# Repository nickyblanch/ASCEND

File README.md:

# ASCEND
All firmware &amp; mechanical design, and documentation for the UArizona SEDS ASCEND! team.

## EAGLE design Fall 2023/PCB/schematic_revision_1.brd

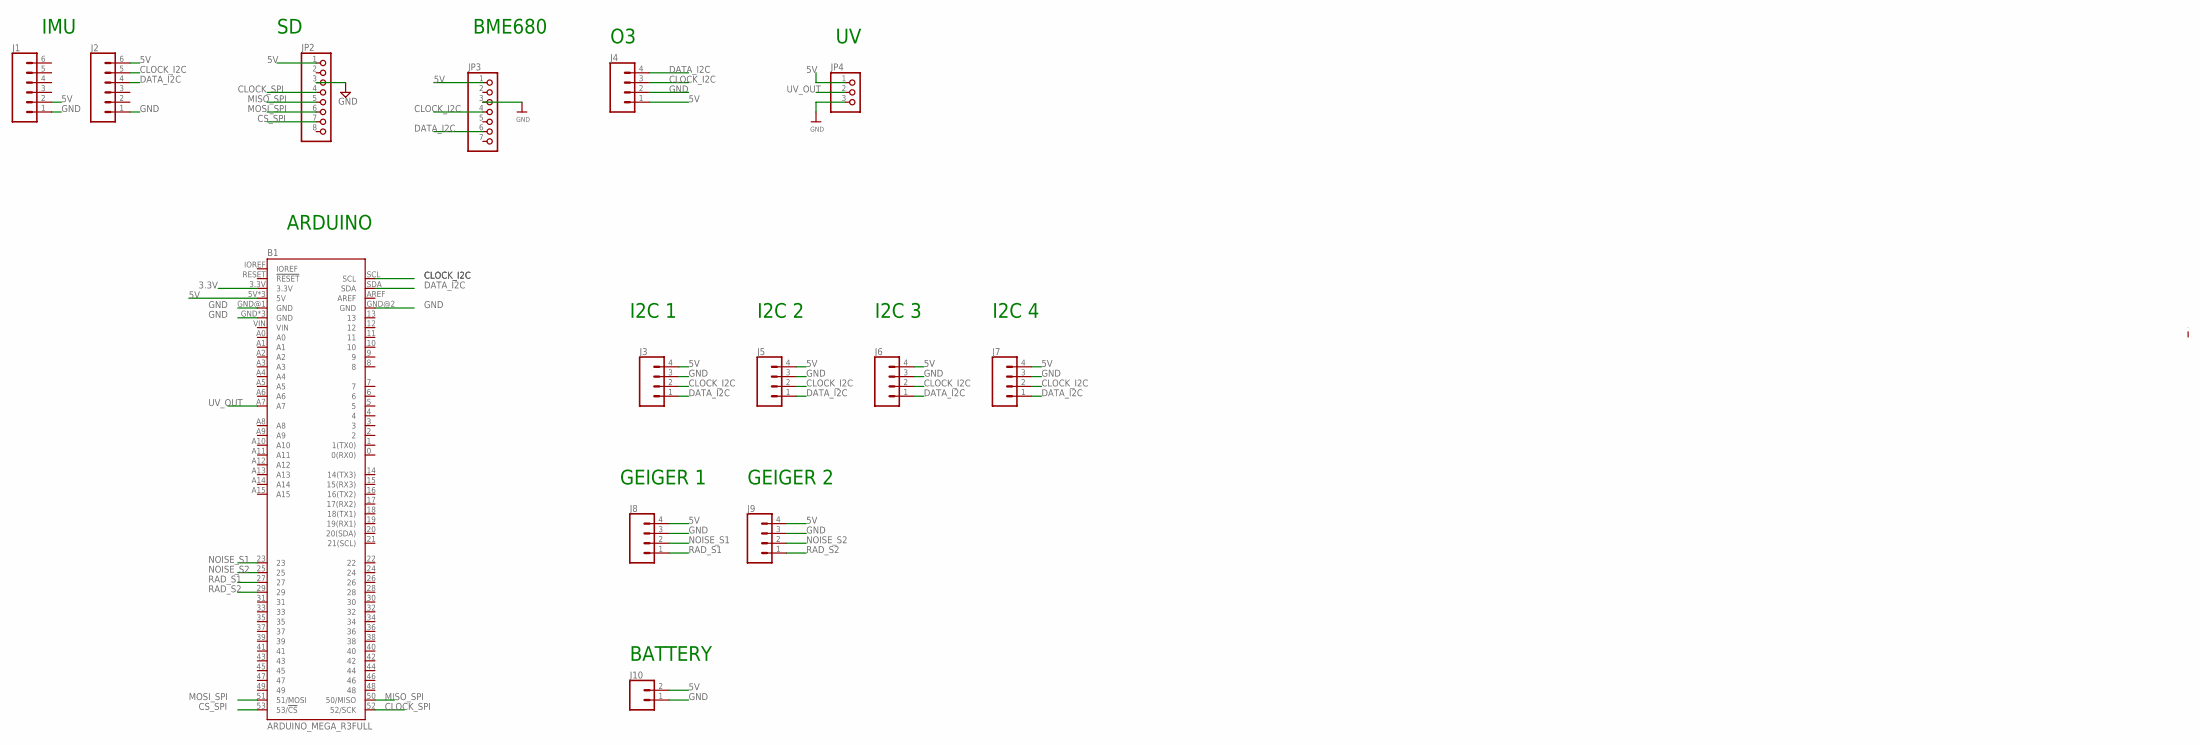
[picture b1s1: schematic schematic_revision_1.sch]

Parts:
B1: ARDUINO_MEGA_R3FULL; ARDUINO_MEGA_NO_SILK
J1, J2: CONN_06NO_SILK_NO_POP; 1X06_NO_SILK
J3, J5, J6, J7, J8, J9: CONN_04PTH; 1X04
J4: CONN_04LOCK; 1X04_LOCK
J10: CONN_02; 1X02
JP2: PINHD-1X8BIG; 1X08-BIG
JP3: HEADER-1X770MIL; 1X07_ROUND_70
JP4: PINHD-1X3CB; 1X03-CLEANBIG

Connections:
3.3V: B1.3.3V
5V: B1.5V, B1.5V@1 (5V), B1.5V@2 (5V), J1.2, J2.6, J3.4, J4.1, J5.4, J6.4, J7.4, J8.4, J9.4, J10.2, JP2.1, JP3.1, JP4.1
CLOCK_I2C: B1.SCL, J2.5, J3.2, J4.3, J5.2, J6.2, J7.2, JP3.4
CLOCK_SPI: B1.52 (52/SCK), JP2.4
CS_SPI: B1.53 (53/!CS), JP2.7
DATA_I2C: B1.SDA, J2.4, J3.1, J4.4, J5.1, J6.1, J7.1, JP3.6
GND: B1.GND, B1.GND@1 (GND), B1.GND@2 (GND), B1.GND@3 (GND), B1.GND@4 (GND), J1.1, J2.1, J3.3, J4.2, J5.3, J6.3, J7.3, J8.3, J9.3, J10.1, JP2.3, JP3.3, JP4.3
MISO_SPI: B1.50 (50/MISO), JP2.5
MOSI_SPI: B1.51 (51/MOSI), JP2.6
NOISE_S1: B1.23, J8.2
NOISE_S2: B1.25, J9.2
RAD_S1: B1.27, J8.1
RAD_S2: B1.29, J9.1
UV_OUT: B1.A7, JP4.2

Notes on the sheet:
IMU
ARDUINO
BME680
I2C 1
I2C 2
I2C 3
I2C 4
GEIGER 1
GEIGER 2
BATTERY

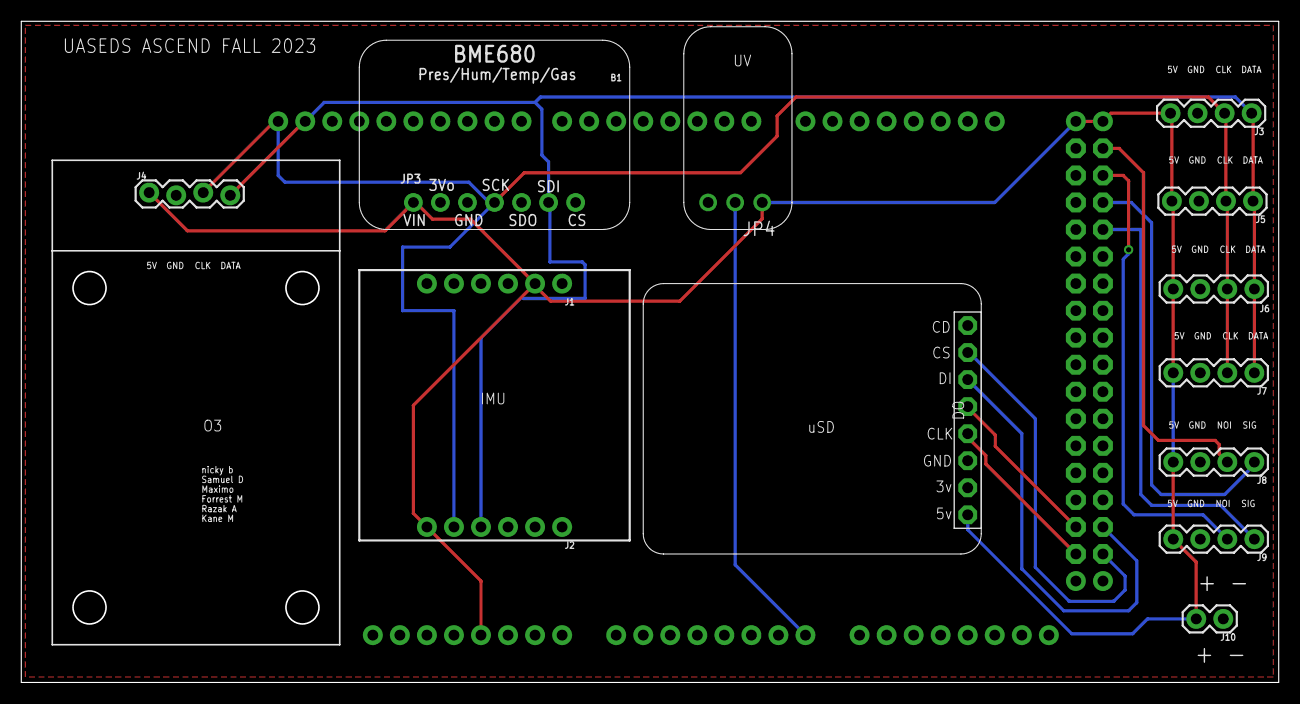
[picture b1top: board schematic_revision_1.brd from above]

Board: 2 copper layers, 118.1 x 62.1 mm, 14 parts (0 on the bottom side), 13 nets.

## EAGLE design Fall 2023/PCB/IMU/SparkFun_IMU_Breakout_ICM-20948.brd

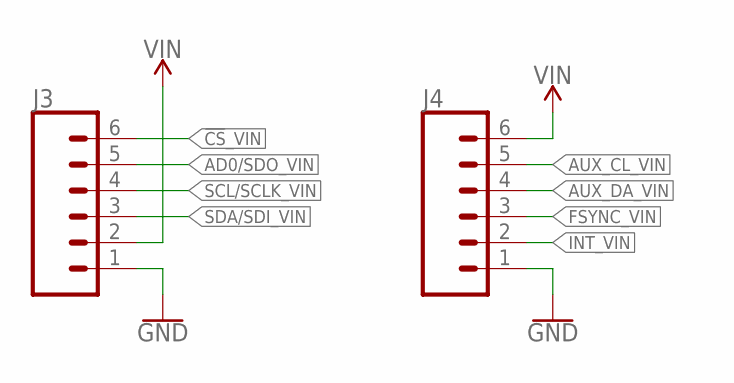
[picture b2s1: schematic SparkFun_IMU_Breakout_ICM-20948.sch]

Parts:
J3, J4: CONN_06NO_SILK_NO_POP; 1X06_NO_SILK

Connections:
!CS!_VIN: J3.6
AD0/SDO_VIN: J3.5
AUX_CL_VIN: J4.5
AUX_DA_VIN: J4.4
FSYNC_VIN: J4.3
GND: J3.1, J4.1
INT_VIN: J4.2
SCL/SCLK_VIN: J3.4
SDA/SDI_VIN: J3.3
VIN: J3.2, J4.6

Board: 2 copper layers, 54 parts (28 on the bottom side), 2 nets, no tracks yet.

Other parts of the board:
U$1, U$2, U$22, U$24: GND4
U$3: PWR0
U$4, U$21: INT3
U$5, U$20: FSNC2
U$6, U$19: ACL1
U$7, U$18: ADA0
U$8: MISO13
U$9: MOSI14
U$10: SCLK15
U$11: #CS16
U$12: 1V8#5V57
U$13, U$30, U$44: VIN5
U$14: NC17
U$15: CL4
U$16: DA2
U$17: AD012
U$23: ADR2
U$25: I2C_PU21
U$26: SPI19
U$27: AUX_PU24
U$28: SFE_LOGO_FLAME_.1
U$29: LED23
U$31: ICM#2094820
U$34, U$40, U$50, U$57: X0
U$35, U$41, U$51, U$58: Y1
U$36, U$42, U$52, U$59: Z2
U$37, U$60: G5
U$38, U$61: A4
U$39, U$49: M3
U$43: QWIIC_9DOF_IMU_0
U$45: I#C1

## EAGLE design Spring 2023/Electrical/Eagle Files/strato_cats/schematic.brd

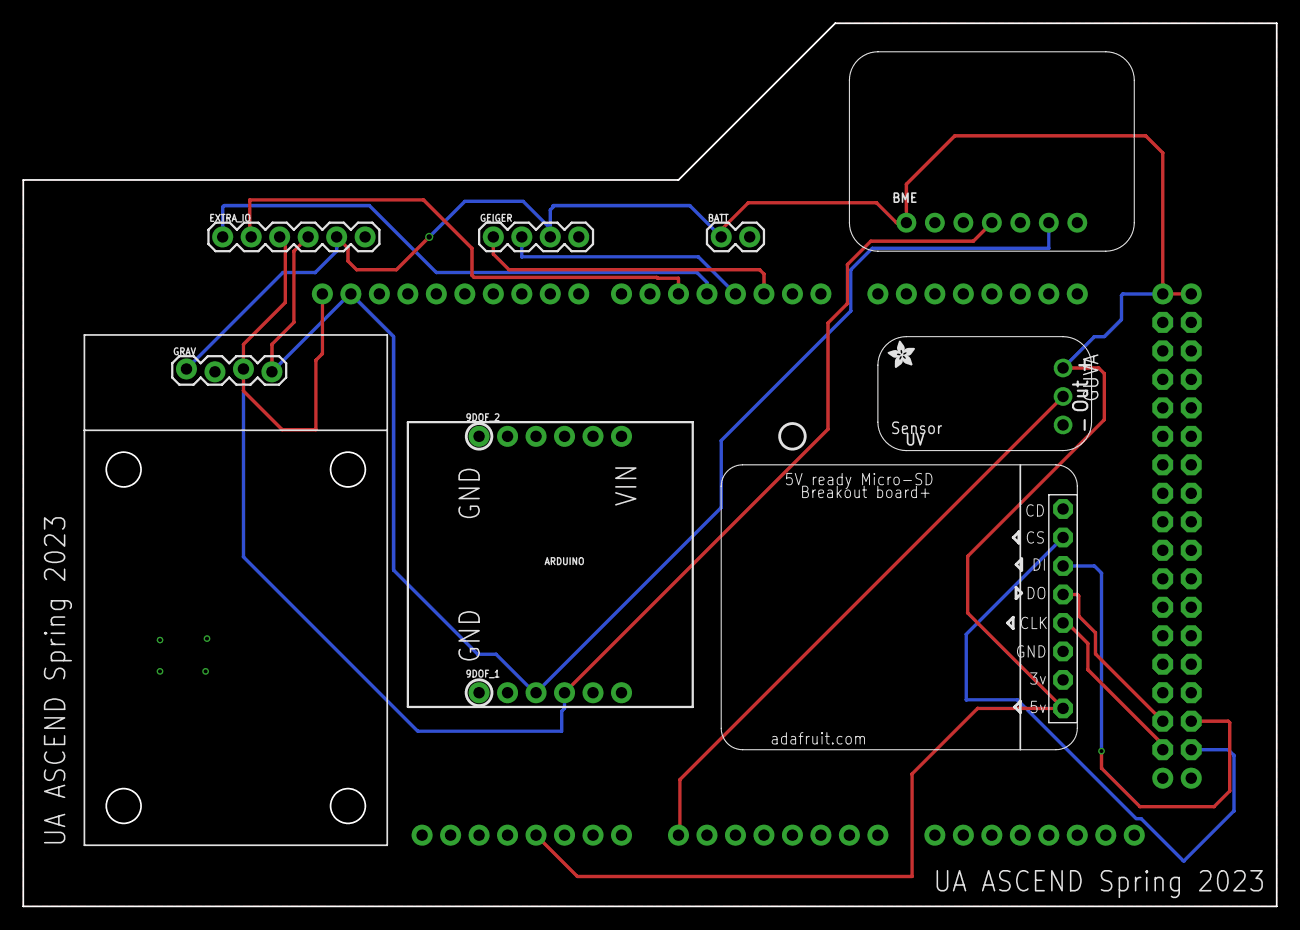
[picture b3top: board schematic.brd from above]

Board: 2 copper layers, 111.8 x 78.7 mm, 12 parts (1 on the bottom side), 13 nets.

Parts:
9DOF_1, 9DOF_2: 1X06_NO_SILK
ARDUINO: ARDUINO_MEGA_R3FULL; ARDUINO_MEGA_NO_SILK
BATT: 1X02
BME: 1X07_ROUND_70
EXTRA_IO: 1X06
GEIGER: 1X04
GRAV: 1X04_LOCK
GUVA: 1X03-CLEANBIG
SD_R: 1X08-BIG
U$15, U$16: ADAFRUIT_2.5MM

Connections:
5V: ARDUINO.5V, ARDUINO.5V@1, ARDUINO.5V@2, BATT.1, BME.1, EXTRA_IO.5, GEIGER.3, GRAV.1, GUVA.1, SD_R.1
CLK: ARDUINO.52, SD_R.4
CS: ARDUINO.53, SD_R.7
D4: ARDUINO.4, EXTRA_IO.1
D5: ARDUINO.5, EXTRA_IO.2
DS: ARDUINO.3, GEIGER.2
GND: 9DOF_1.1, 9DOF_2.1, ARDUINO.GND, ARDUINO.GND@1, ARDUINO.GND@2, ARDUINO.GND@3, ARDUINO.GND@4, BATT.2, BME.3, EXTRA_IO.6, GEIGER.4, GRAV.2, GUVA.3, SD_R.3
unnamed: ARDUINO.A0, GUVA.2
NS: ARDUINO.2, GEIGER.1
SCL: 9DOF_1.4, ARDUINO.SCL, BME.4, EXTRA_IO.3, GRAV.3
SDA: 9DOF_1.3, ARDUINO.SDA, BME.6, EXTRA_IO.4, GRAV.4
SDI: ARDUINO.51, SD_R.6
SDO: ARDUINO.50, SD_R.5

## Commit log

2023-02-25 initial files
2023-02-25 Basic Code
2023-02-25 removing unnecessary files
2023-02-25 Code add
2023-02-25 removed bmp from code
2023-02-25 Mechanical
    mechanical design stuff
2023-02-25 new design blocks
2023-02-25 added mics part
2023-02-25 did the schematic
2023-03-02 finished board
2023-03-03 final board !
2023-03-10 not sure what changed
2023-03-17 mechanical design update
2023-03-17 Lid update
2023-03-18 Lid (actual fix)
2023-03-18 Lid (actually actually works)
2023-03-22 DFRobot libary and new Gravity file
2023-03-25 Update Gravity Sensor
2023-03-25 Gravity Sensor Working
2023-03-25 Friday Code
2023-03-30 allows printing to serial, led support also
2023-03-30 changed sd flash code
2023-04-01 removed delay
2023-04-02 data
2023-04-03 Website visualiser
2023-04-04 3d Visualization added
2023-04-07 2d-3d transition bugfixes
2023-04-08 spacing fix
2023-09-29 Data vis moved
2023-09-29 Fall 23 folder with last sem code
2023-09-29 Basic Commit
2023-10-21 fresh start
2023-10-21 small fix for return
2023-10-21 update files
2023-10-21 Updated with geiger libraries
2023-10-21 example for geiger
2023-10-21 Worked a bit on the Geiger Counter code
2023-10-27 mics
2023-10-27 SD Code
2023-10-28 SD Card changes, Sound sensor written
2023-10-28 GUVA -max
2023-11-03 Gravity o3 Sensor code
2023-11-04 capitalization
2023-11-04 bem60s (razak)
2023-11-04 ICM Cleaning
2023-11-04 Headers and cleaning
2023-11-04 bme6802 address update
2023-11-08 V 1.0, Everything is tidy
2023-11-15 Small evertwhere. ICM, Geiger todo
2023-11-16 Fix data type conversion issue and add file naming functionality
2023-11-16 Add file upload functionality to data visualization page
2023-11-16 LED Error codes and retry connection behaviour
2023-11-17 Document sensors + null writes
2023-11-18 reversion to stop error
2024-01-20 Spring 2024 Commit
2024-01-20 environment change to nano every
2024-02-16 data ?
2024-02-16 TODO
2024-03-15 Move definitions to def.h
2024-03-19 step 1
2024-03-20 all working but geiger
2024-09-27 Code Framework Created
2024-10-25 added todo, sd card code
2024-10-25 added spectral demo
2024-10-25 fixed dependencies, added spectral sensor code
2024-10-25 minor spectral sensor change
2024-11-08 Many things
2025-02-07 Fall code
2025-02-07 Fixed weird stuff, added Sensor Helper
2025-02-14 Added sensor functions, updated todo and cleaned
2025-02-21 Temp, Spectral, Infra, Air quality
2025-02-28 Tested and validated IR, Visible, Temp, IMU, UV
2025-03-07 WIRE!!!!!
2025-03-08 Data writing. Dependencies fucked
2025-03-28 Changes to make program fit
2025-04-25 Final Code
2025-05-03 fixed dependencies
2025-10-03 Fall 2025 Created
2025-10-03 Updated TODO f25
2025-10-03 Updated IMU
2025-10-10 INA260 implemented
2025-10-24 Added neopixel code
2026-02-27 idk a lot
2026-03-26 Added triple spectral sensor

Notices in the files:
parts and their libraries:
SparkFun-Connectors: Licensing: Creative Commons ShareAlike 4.0 International - https://creativecommons.org/licenses/by-sa/4.0
microbuilder: This work is placed in the public domain, and may be freely used for commercial and non-commercial work with the following conditions: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
